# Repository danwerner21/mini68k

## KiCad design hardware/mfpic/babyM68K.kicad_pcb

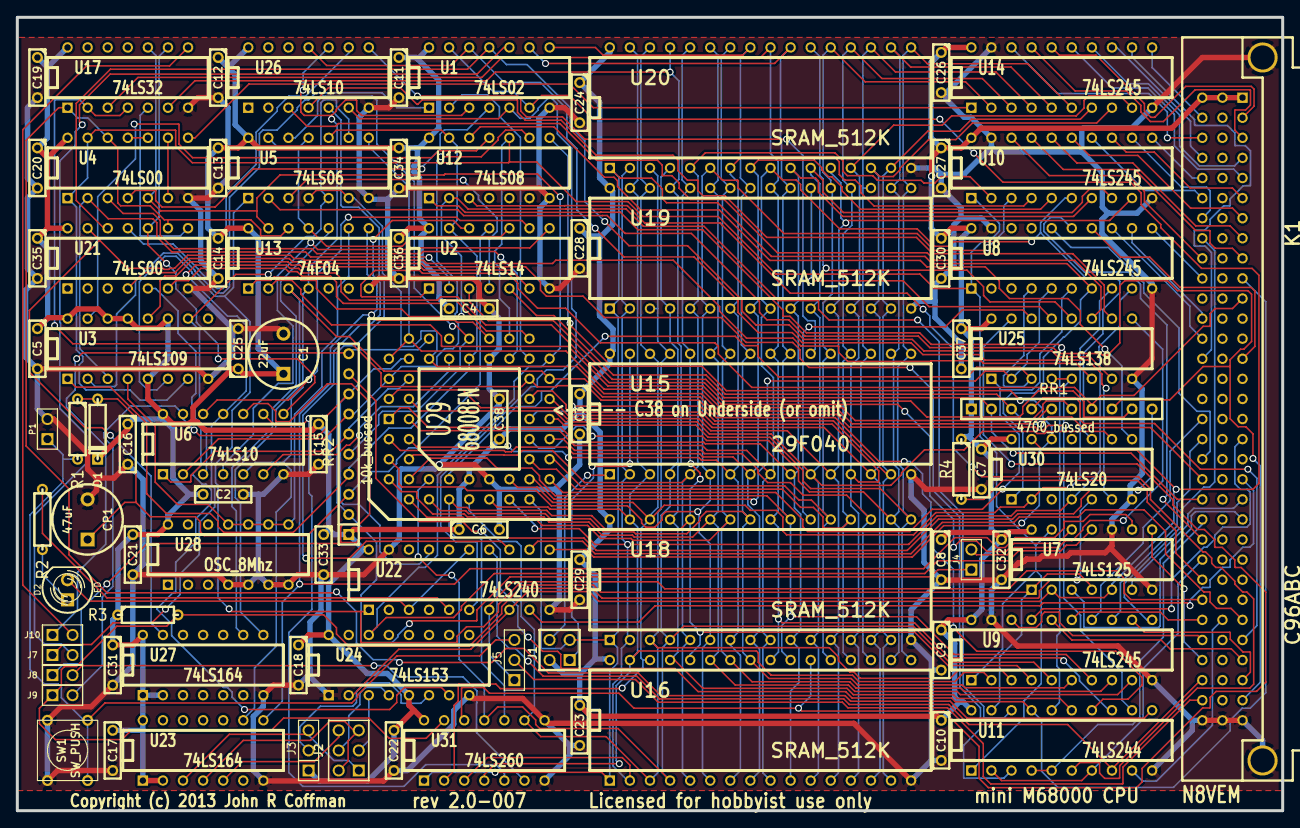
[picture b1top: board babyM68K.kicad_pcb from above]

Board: 2 copper layers, 160.0 x 100.3 mm, 90 parts (0 on the bottom side), 163 nets.

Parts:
C1: 22uF; C2V8
C2, C3, C4, C5, C6, C7, C8, C9, C10, C11, C12, C13, C14, C15, C16, C17, C18, C19, C20, C21, C22, C23, C24, C25, C26, C27, C28, C29, C30, C31, C32, C33, C34, C35, C36, C37, C38: .1uF; C2
CP1: 47uF; C2V8
D1: BAT43; D3
D2: LED; LED-5MM-POL
J1: FLSH/EPR; PIN_ARRAY_2X2
J2: WAIT; pin_array_3x2
J3: MemW-WS; PIN_ARRAY_3X1
J4, J7, J8, J9, J10: CONN_2; PIN_ARRAY_2X1
J5: CONN_3; PIN_ARRAY_3X1
K1: C96ABC; C96ABCMC_52
P1: CONN_2; PIN_ARRAY_2X1
R1: 10; R3
R2: 47; R3
R3: 47K; R3
R4: 4700; R3
RR1: 4700_bussed; r_pack9
RR2: 10k_bussed; r_pack9
SW1: SW_PUSH; SW_PUSH_SMALL
U1: 74LS02; DIP-14__300_52
U2: 74LS14; DIP-14__300_52
U3: 74LS109; DIP-16__300_52
U4, U21: 74LS00; DIP-14__300_52
U5: 74LS06; DIP-14__300_52
U6, U26: 74LS10; DIP-14__300_52
U7: 74LS125; DIP-14__300_52
U8, U9, U10, U14: 74LS245; DIP-20__300_52
U11: 74LS244; DIP-20__300_52
U12: 74LS08; DIP-14__300_52
U13: 74F04; DIP-14__300_52
U15: 29F040; DIP-32__600_52
U16, U18, U19, U20: SRAM_512K; DIP-32__600_52
U17: 74LS32; DIP-14__300_52
U22: 74LS240; DIP-20__300_52
U23, U27: 74LS164; DIP-14__300_52
U24: 74LS153; DIP-16__300_52
U25: 74LS138; DIP-16__300_52
U28: OSC_8Mhz; DIP-14__300_52
U29: 68008FN; PLCC52_52
U30: 74LS20; DIP-14__300_52
U31: 74LS260; DIP-14__300_52

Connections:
/AS: U11.12, U13.3, U25.4, U25.5, U27.8, U29.31
/BERR: J10.1, RR2.10, U29.44
/BG: U1.2, U29.35
/BGACK: U3.7, U4.1, U4.13, U7.13, U8.1, U9.1, U10.1, U11.1, U12.10, U29.36
/BR: U4.3, U29.37
/CLK: U3.4, U13.9, U28.8, U28.9, U28.10, U28.11
/CSRAM0: U16.22, U25.15, U31.12
/CSRAM1: U18.22, U25.14
/CSRAM2: U19.22, U25.13
/CSRAM3: U20.22, U25.12
/DS: U11.14, U17.2, U17.4, U29.32
/DTACK: U21.6, U29.34
/HALT: RR2.5, U5.12, U29.40
/IPL0: RR1.6, U5.8, U29.46, U29.47
/IPL1: RR1.5, U5.4, U5.6, U29.45
/Memory//USERLOWMEM: U6.8, U17.9, U21.10
/POClear: U13.10, U27.9
/RD: U11.13, U15.24, U16.24, U17.3, U18.24, U19.24, U20.24
/RESET: RR2.4, U2.13, U3.1, U5.10, U12.13, U29.41
/ROM: U15.22, U26.8
/Reset//RESET_IN: J5.3, P1.1, R1.2, SW1.2
/Select//IOSPACE: U1.12, U26.11, U30.6
/Select//ROMONLY: U21.13, U25.6, U27.13
/Select/PU-10K-A: J4.1, RR2.2, U26.5
/Tranceivers/D_OUT: U4.8, U14.1
/Tranceivers/LOCAL: U1.4, U4.4
/VPA: U6.6, U29.43
/WAIT: U11.3, U21.4
/WR: U11.15, U16.29, U17.6, U18.29, U19.29, U20.29
/Wait_State/1WS: J2.1, J3.3, U23.3
/Wait_State/2WS: J2.2, J2.5, U23.4
/Wait_State/3WS: J2.6, U23.5
/Wait_State/RDY: U21.5, U24.7
/Wait_State/WS-IORD: J2.3, U24.3
/Wait_State/WS-IOWR: J2.4, U24.4
A0: U10.9, U15.12, U16.12, U18.12, U19.12, U20.12, U29.51
A1: U10.8, U15.11, U16.11, U18.11, U19.11, U20.11, U29.52, U30.9
A2: U10.7, U15.10, U16.10, U18.10, U19.10, U20.10, U29.1
A3: U10.6, U15.9, U16.9, U18.9, U19.9, U20.9, U29.2, U30.10
A4: U10.5, U15.8, U16.8, U18.8, U19.8, U20.8, U29.3
A5: U10.4, U15.7, U16.7, U18.7, U19.7, U20.7, U29.4
A6: U10.3, U15.6, U16.6, U18.6, U19.6, U20.6, U29.5
A7: U10.2, U15.5, U16.5, U18.5, U19.5, U20.5, U29.6
A8: U9.9, U15.27, U16.27, U18.27, U19.27, U20.27, U29.7
A9: U9.8, U15.26, U16.26, U18.26, U19.26, U20.26, U29.8
A10: U1.9, U9.7, U15.23, U16.23, U18.23, U19.23, U20.23, U29.9
A11: U1.8, U9.6, U15.25, U16.25, U18.25, U19.25, U20.25, U29.10
A12: U9.5, U15.4, U16.4, U18.4, U19.4, U20.4, U29.11, U31.11
A13: U9.4, U15.28, U16.28, U18.28, U19.28, U20.28, U29.12, U31.10
A14: U9.3, U15.29, U16.3, U18.3, U19.3, U20.3, U29.14, U31.9
A15: U9.2, U15.3, U16.31, U18.31, U19.31, U20.31, U29.16, U31.4
A16: U8.9, U15.2, U16.2, U18.2, U19.2, U20.2, U29.18, U30.4, U31.3
A17: U8.8, U15.30, U16.30, U18.30, U19.30, U20.30, U29.19, U30.2, U31.2
A18: J1.3, U8.7, U16.1, U18.1, U19.1, U20.1, U29.20, U30.1, U31.1
A19: U8.6, U25.1, U29.21
A20: U8.5, U25.2, U29.22
A21: U8.4, U25.3, U29.13
AS: U1.3, U6.5, U13.4, U23.9, U26.10
BUSAK: U3.6, U5.1, U7.1, U7.4, U11.19, U22.1
B_/BUSAK: K1.A31, RR1.8, U5.2
B_/BUSRQ: K1.A11, RR1.7, U2.1
B_/CLK: K1.C29, U7.8
B_/HALT: K1.C25, R4.2
B_/INT: K1.C21, RR1.2, U2.3
B_/IORQ: K1.A27, U22.12
B_/M1: K1.A20, U22.9
B_/MREQ: K1.C30, U11.8, U22.14
B_/NMI: K1.C20, RR1.3, U2.5
B_/RD: K1.C24, U11.2, U11.7
B_/RESET: J5.2, K1.C31
B_/RESOUT: J5.1, K1.C26, U22.7
B_/RFSH: K1.A28, RR1.4
B_/WAIT: K1.A10, RR2.9, U11.17
B_/WR: K1.C22, U11.4, U11.5
B_A0: K1.C5, U10.11
B_A1: K1.C7, U10.12
B_A2: K1.A6, U10.13
B_A3: K1.C6, U10.14
B_A4: K1.A7, U10.15
B_A5: K1.A8, U10.16
B_A6: K1.A9, U10.17
B_A7: K1.C9, U10.18
B_A8: K1.C8, U9.11
B_A9: K1.A30, U9.12
B_A10: K1.C18, U9.13
B_A11: K1.C17, U9.14
B_A12: K1.C27, U9.15
B_A13: K1.A29, U9.16
B_A14: K1.A18, U9.17
B_A15: K1.C28, U9.18
B_A16: K1.C10, U8.11
B_A17: K1.C12, U8.12
B_A18: K1.C13, U8.13
B_A19: K1.A14, U8.14
B_A20: K1.C23, U8.15
B_A21: K1.C19, U8.16
B_A22: K1.A21, U7.6
B_A23: K1.A22, U7.3
B_D0: K1.C2, U14.11
B_D1: K1.C14, U14.12
B_D2: K1.C4, U14.13
B_D3: K1.A4, U14.14
B_D4: K1.A5, U14.15
B_D5: K1.A2, U14.16
B_D6: K1.A3, U14.17
B_D7: K1.C3, U14.18
B_DT/R: K1.B27, U11.9
CLK: U7.9, U13.8, U23.8, U29.38
D0: U14.9, U15.13, U16.13, U18.13, U19.13, U20.13, U29.30
D1: U14.8, U15.14, U16.14, U18.14, U19.14, U20.14, U29.29
D2: U14.7, U15.15, U16.15, U18.15, U19.15, U20.15, U29.28
D3: U14.6, U15.17, U16.17, U18.17, U19.17, U20.17, U29.27
D4: U14.5, U15.18, U16.18, U18.18, U19.18, U20.18, U29.26
D5: U14.4, U15.19, U16.19, U18.19, U19.19, U20.19, U29.25
D6: U14.3, U15.20, U16.20, U18.20, U19.20, U20.20, U29.24
D7: U14.2, U15.21, U16.21, U18.21, U19.21, U20.21, U29.23
FC0: RR2.6, U6.1, U29.50
FC1: RR2.7, U6.2, U12.9, U29.49
FC2: J9.2, RR2.8, U6.13, U22.17, U29.48
GND: C1.2, C2.2, C3.2, C4.2, C5.2, C6.2, C7.2, C8.2, C9.2, C10.2, C11.2, C12.2, C13.2, C14.2, C15.2, C16.2, C17.2, C18.2, C19.2, C20.2, C21.2, C22.2, C23.2, C24.2, C25.2, C26.2, C27.2, C28.2, C29.2, C30.2, C31.2, C32.2, C33.2, C34.2, C35.2, C36.2, C37.2, C38.2, CP1.2, K1.A32, K1.B32, K1.C32, K1.HOLE, P1.2, SW1.1, U1.7, U2.7, U3.8, U4.7, U5.7, U6.7, U7.7, U7.10, U8.10, U8.19, U9.10, U9.19, U10.10, U10.19, U11.10, U12.7, U13.7, U14.10, U14.19, U15.16, U16.16, U17.7, U18.16, U19.16, U20.16, U21.7, U22.10, U22.19, U23.7, U24.1, U24.8, U25.8, U26.7, U27.7, U28.4, U28.5, U28.6, U28.7, U29.17, U29.39, U30.7, U31.7, U31.8
IORQ: U1.6, U1.13, U7.2, U7.5, U22.8, U24.2, U30.13
M1: U12.8, U22.11, U30.12
MREQ: U1.5, U22.6, U26.6
unnamed: U21.11, U26.9
unnamed: U1.11, U21.12, U25.7
unnamed: J4.2, U25.9
unnamed: U25.10, U26.4
unnamed: U25.11, U26.3
unnamed: J3.2, U24.6
unnamed: R2.1, U22.5
unnamed: D2.1, R2.2
unnamed: D2.2, U22.3, U22.15
unnamed: U2.10, U5.11, U5.13, U13.11
unnamed: J1.4, U15.1
unnamed: J8.2, U31.6
unnamed: U17.5, U21.8
unnamed: J1.1, U15.31
unnamed: U6.9, U31.5
unnamed: J7.2, U1.10
unnamed: J10.2, U17.8
unnamed: U11.16, U12.1
unnamed: U11.18, U12.2, U13.1
unnamed: U11.6, U12.3
unnamed: U4.10, U4.11
unnamed: U7.12, U13.2
unnamed: U4.6, U4.9
unnamed: U12.12, U30.8
unnamed: U3.10, U5.5, U5.9, U6.3
unnamed: U3.15, U12.11
unnamed: U2.6, U3.12
unnamed: U2.4, U5.3
unnamed: U2.8, U6.4
unnamed: U2.9, U6.12
unnamed: U2.2, U3.3, U4.2
unnamed: U1.1, U3.2
PU-10K-clear: CP1.1, D1.1, R1.1, RR2.3, U2.11
PU_MEM4K/1K: J7.1, RR1.9, U6.11
PU_MEM64K/4K: J8.1, RR1.10, U6.10
R/W: U4.5, U7.11, U13.13, U17.10, U24.14, U29.33
RESET: U2.12, U22.13
SUPV/USER: J9.1, R3.2, U30.5, U31.13
VCC: C1.1, C2.1, C3.1, C4.1, C5.1, C6.1, C7.1, C8.1, C9.1, C10.1, C11.1, C12.1, C13.1, C14.1, C15.1, C16.1, C17.1, C18.1, C19.1, C20.1, C21.1, C22.1, C23.1, C24.1, C25.1, C26.1, C27.1, C28.1, C29.1, C30.1, C31.1, C32.1, C33.1, C34.1, C35.1, C36.1, C37.1, C38.1, D1.2, J1.2, J3.1, K1.A1, K1.B1, K1.C1, R3.1, R4.1, RR1.1, RR2.1, U1.14, U2.14, U3.5, U3.11, U3.13, U3.14, U3.16, U4.14, U5.14, U6.14, U7.14, U8.20, U9.20, U10.20, U11.20, U12.14, U13.14, U14.20, U15.32, U16.32, U17.14, U18.32, U19.32, U20.32, U21.14, U22.20, U23.1, U23.2, U23.14, U24.5, U24.16, U25.16, U26.14, U27.1, U27.2, U27.14, U28.14, U29.15, U30.14, U31.14
W/R: U4.12, U11.11, U13.12, U17.1, U21.9

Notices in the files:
hardware/mfpic/babyM68K.kicad_pcb:
Copyright (c) 2013 John R Coffman
